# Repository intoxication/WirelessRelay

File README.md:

# Wireless Relay
Esp8266, Maple Mini powered wireless relay with up to 14 outputs

# Firmware 
Designed to run on maple mini (or clone) the device listens to local broadcast packets on port 15000

# Software
Runs under mono/C# allows users to control and query wireless device

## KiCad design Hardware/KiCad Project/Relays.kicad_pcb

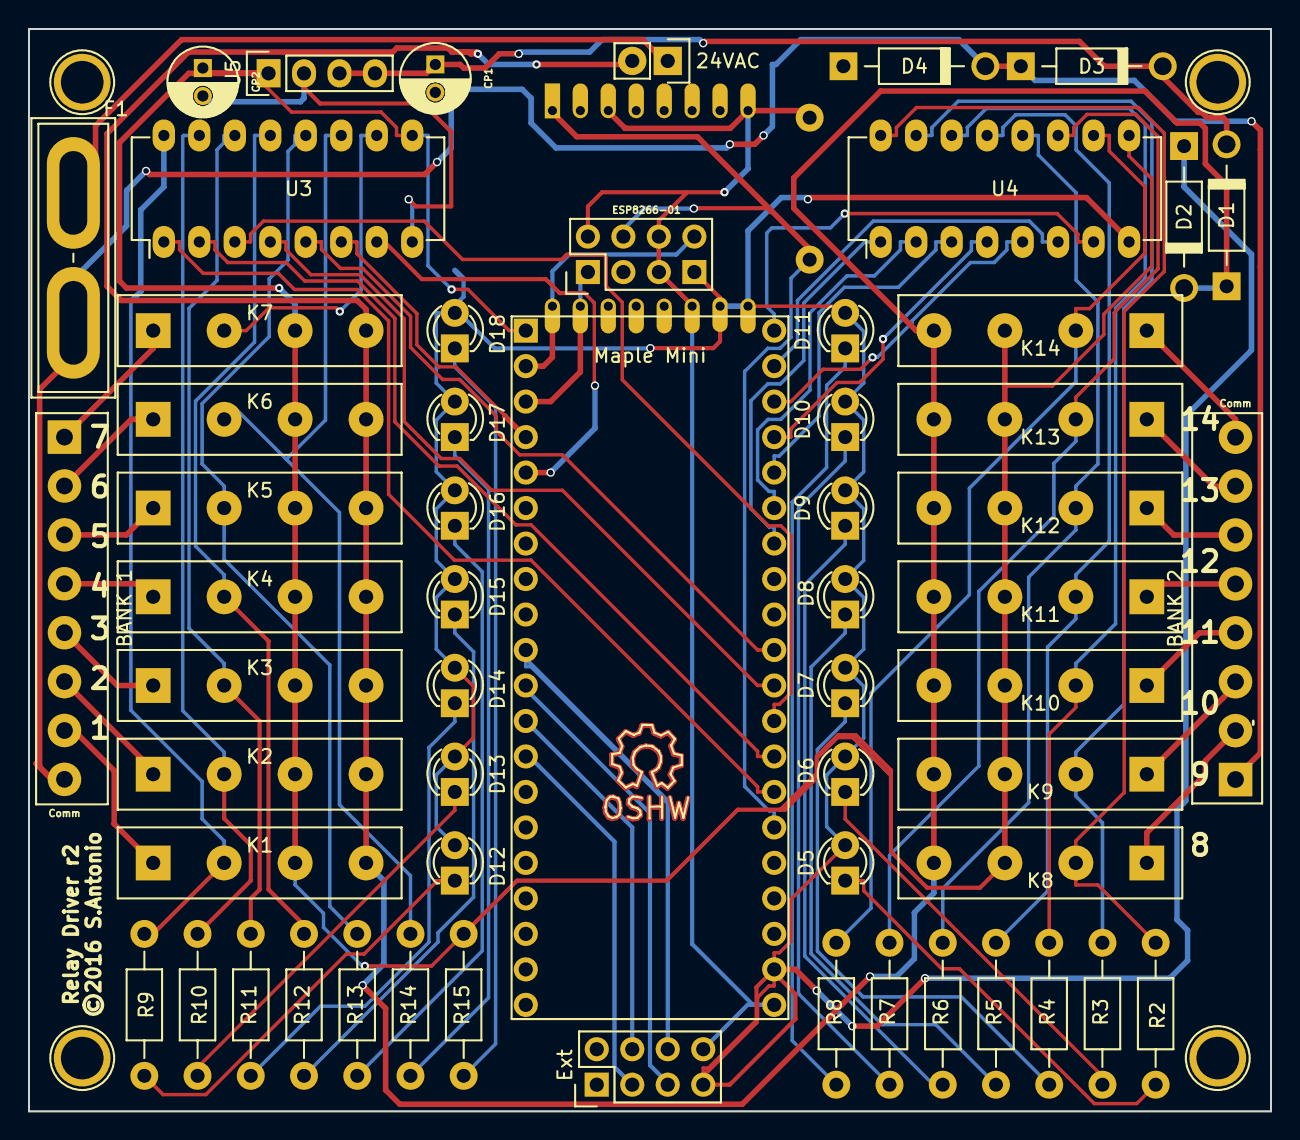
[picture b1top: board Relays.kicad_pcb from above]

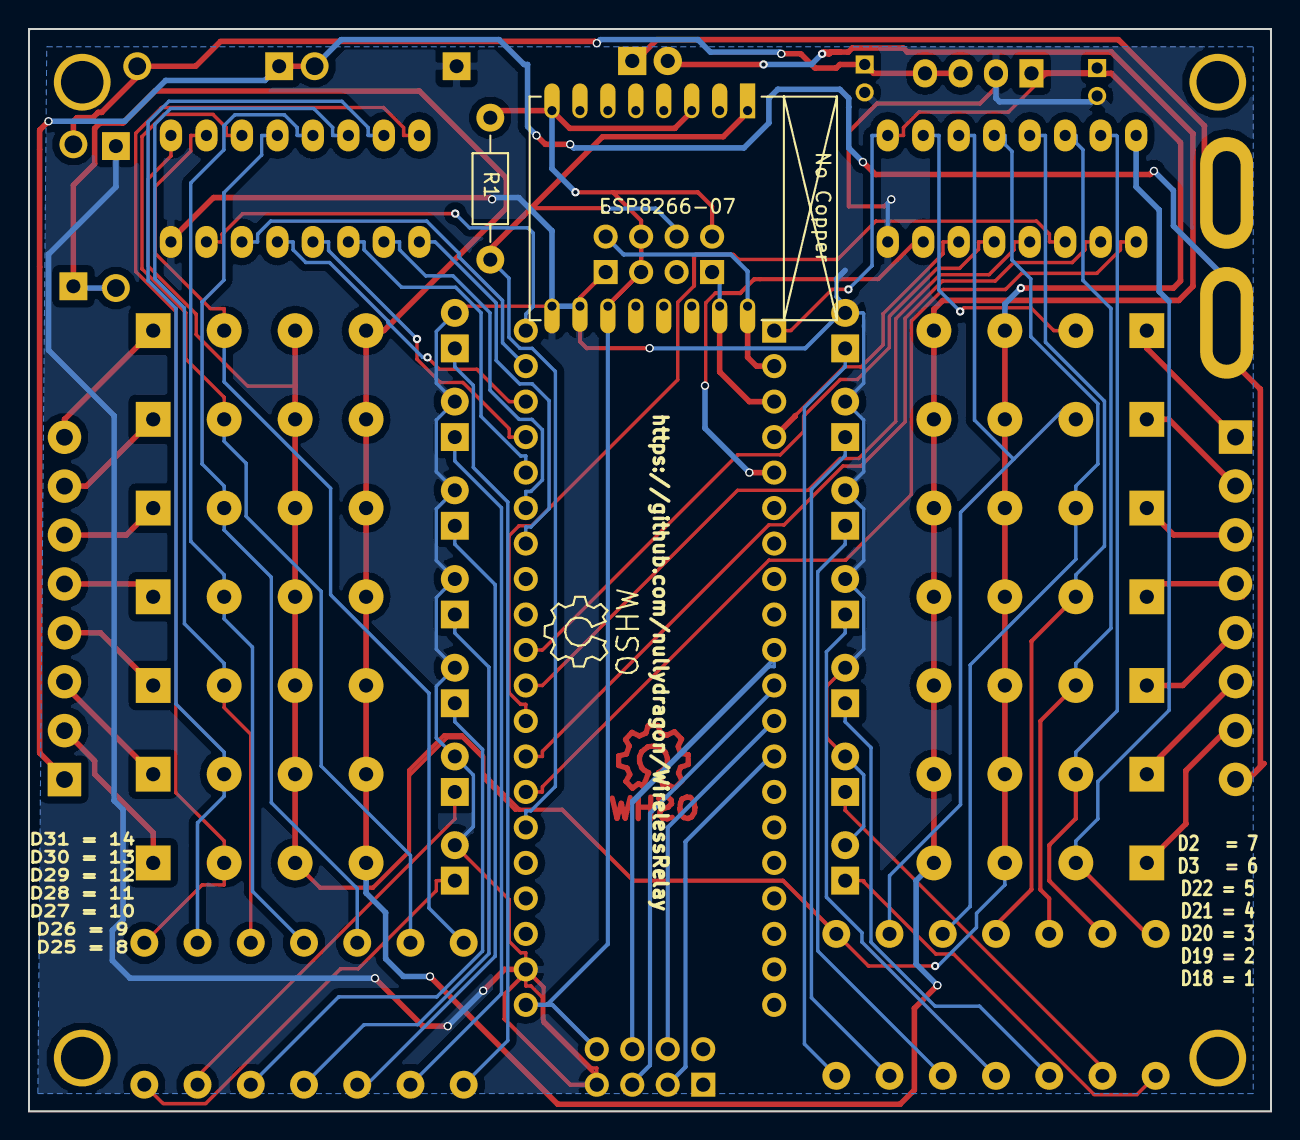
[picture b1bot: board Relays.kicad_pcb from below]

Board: 2 copper layers, 88.9 x 77.5 mm, 67 parts (3 on the bottom side), 69 nets.

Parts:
BANK 1, BANK 2: Comm; TerminalBlock_Pheonix_PT-3.5mm_8pol
CP1: CP1; C_Radial_D5_L11_P2
CP2: CP2; C_Radial_D5_L11_P2
D1, D2, D3, D4: DIODE; Diode_DO-41_SOD81_Horizontal_RM10
D5, D6, D7, D8, D9, D10, D11, D12, D13, D14, D15, D16, D17, D18: LED; LED-3MM
ESP8266-01: ESP8266-02; Pin_Header_Straight_2x04
ESP8266-07: ESP-07v2
F1: BladeFuse-CarType
K1, K2, K3, K4, K5, K6, K7, K8, K9, K10, K11, K12, K13, K14: SIP-1A05
LOGO1, LOGO2: Symbol_OSHW-Logo_SilkScreen
LOGO3: Symbol_OSHW-Logo_CopperTop
MNT1, MNT2, MNT3, MNT4: 1pin
Maple Mini: Maple Mini; Pin_Header_Straight_2x20
P1: 24VAC; Pin_Header_Straight_1x02
P2: Ext; Pin_Header_Straight_2x04
R1: 10k; Resistor_Horizontal_RM10mm
R2, R3, R4, R5, R6, R7, R8, R9, R10, R11, R12, R13, R14, R15: R; Resistor_Horizontal_RM10mm
U3, U4: ULN2003AN; DIP-16_W7.62mm_LongPads
U5: D24V3F5; Pin_Header_Straight_1x04

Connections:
+3.3V: ESP8266-01.2, ESP8266-01.5, ESP8266-01.6, ESP8266-07.3, ESP8266-07.8, ESP8266-07.11, Maple Mini.40, P2.8, R1.1
+5V: CP2.1, K1.3, K2.3, K3.3, K4.3, K5.3, K6.3, K7.3, K8.3, K9.3, K10.3, K11.3, K12.3, K13.3, K14.3, Maple Mini.1, R15.1, U3.9, U4.9, U5.1
+36V: CP1.1, D1.2, D3.2, U5.3, U5.4
/AC1: D1.1, D2.2, K1.4, K2.4, K3.4, K4.4, K5.4, K6.4, K7.4, K8.4, K9.4, K10.4, K11.4, K12.4, K13.4, K14.4, P1.2
/AC2: BANK 1.8, BANK 2.1, D3.1, D4.2, F1.1, F1.2, P1.1
/D8: Maple Mini.19, P2.6
/D9: Maple Mini.21, P2.5
/D10: Maple Mini.23, P2.4
/D11: Maple Mini.25, P2.3
/D17: ESP8266-01.4, ESP8266-07.1, Maple Mini.30, R1.2
/D18: Maple Mini.28, U3.1
/D19: Maple Mini.26, U3.2
/D20: Maple Mini.24, U3.3
/D21: Maple Mini.22, U3.4
/D22: Maple Mini.20, U3.5
/D23: Maple Mini.7, U3.6
/D24: Maple Mini.9, U3.7
/D25: Maple Mini.14, U4.1
/D26: Maple Mini.12, U4.2
/D27: Maple Mini.10, U4.3
/D28: Maple Mini.8, U4.4
/D29: Maple Mini.6, U4.5
/D30: Maple Mini.4, U4.6
/D31: Maple Mini.2, U4.7
/RL1: K8.2, R2.1, U4.16
/RL2: K9.2, R3.1, U4.15
/RL3: K10.2, R4.1, U4.14
/RL4: K11.2, R5.1, U4.13
/RL5: K12.2, R6.1, U4.12
/RL6: K13.2, R7.1, U4.11
/RL7: K14.2, R8.1, U4.10
/RL8: K1.2, R9.1, U3.16
/RL9: K2.2, R10.1, U3.15
/RL10: K3.2, R11.1, U3.14
/RL11: K4.2, R12.1, U3.13
/RL12: K5.2, R13.1, U3.12
/RL13: K6.2, R14.1, U3.11
/RX3: ESP8266-01.8, ESP8266-07.16, Maple Mini.3
/TX3: ESP8266-01.1, ESP8266-07.15, Maple Mini.5
GND: CP1.2, CP2.2, D2.1, D4.1, D5.2, D6.2, D7.2, D8.2, D9.2, D10.2, D11.2, D12.2, D13.2, D14.2, D15.2, D16.2, D17.2, D18.2, ESP8266-01.7, ESP8266-07.9, ESP8266-07.10, Maple Mini.38, P2.7, U3.8, U4.8, U5.2
unnamed: D5.1, R2.2
unnamed: D6.1, R3.2
unnamed: D7.1, R4.2
unnamed: D8.1, R5.2
unnamed: D9.1, R6.2
unnamed: D10.1, R7.2
unnamed: D11.1, R8.2
unnamed: D12.1, R9.2
unnamed: D13.1, R10.2
unnamed: D14.1, R11.2
unnamed: D15.1, R12.2
unnamed: D16.1, R13.2
unnamed: D17.1, R14.2
unnamed: D18.1, R15.2
unnamed: BANK 1.7, K1.1
unnamed: BANK 1.6, K2.1
unnamed: BANK 1.5, K3.1
unnamed: BANK 1.4, K4.1
unnamed: BANK 1.3, K5.1
unnamed: BANK 1.2, K6.1
unnamed: BANK 1.1, K7.1
unnamed: K7.2, U3.10
unnamed: BANK 2.2, K8.1
unnamed: BANK 2.3, K9.1
unnamed: BANK 2.4, K10.1
unnamed: BANK 2.5, K11.1
unnamed: BANK 2.6, K12.1
unnamed: BANK 2.7, K13.1
unnamed: BANK 2.8, K14.1

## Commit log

2016-01-20 init repo
    add git ignore
2016-01-20 Add wireless relay hardware files for use with KiCAD
2016-01-20 Add C# command and control software
2016-01-20 add maple mini firmware to run the wireless relay board
2016-01-31 tweaked firmware broadcast to send status of device
2016-02-03 added esp826601 bigger headers and fuse
2016-02-03 tweaked silkscreen and footprints slightly
2016-02-03 fixes silk screen

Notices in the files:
Hardware/KiCad Project/Relays.kicad_pcb:
©2016 S.Antonio
